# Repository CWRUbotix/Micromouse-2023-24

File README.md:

# Micromouse 2023-24 🐁

A fully autonomous maze-solving not-quite-mouse-sized robot. 

## Folders

```
.
├── LICENSE	     # License (woohoo)
├── README.md    # This file
├── cad          # 3D-models and designs
├── pcb          # Hardware-related designs and component docs
└── software     # Soft/firmware for the robot
```

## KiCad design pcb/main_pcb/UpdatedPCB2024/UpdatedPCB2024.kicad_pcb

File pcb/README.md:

# Hardware Docs & Meeting Notes

The PCB for this year's Micromouse robot makes use of several pre-built modules to simplify the pCB design. The motor drivers, accel/gyro, and Teensy 4.1 are "socketed" using headers while a custom buck/boost converter is used to generate the 5V and 3V3 rails needed by everything.

## 10/9

### TODO

* find gyro - probably i squared c 
* create Teensy on kicad
* find / reverse engineering motor controllers (DRV8871) schematics

### Parts :

* Should have
  - 6 sensors with 2 pins for i squared c and ground (software placement)
  - A voltage regulator 
  - i squared c "I2C" - protocol that is bi directional 
  - JST connectors
  - Teensy 4.1 : powerful microcontroller 
  - motor controllers : h bridge clip with capacitors 
    + can integrate into the board or kept it separate and connect manually
    + jst connectors
  - power switch
  - reset switch
  - gyro : type of sensor 
* Nice to have
  - battery protection : not required but nice to have
  - dip switches to go into debugging mode (nice to have)
  - leds for general debugging (nice to have)
  - whiteboard for labeling (nice to have)

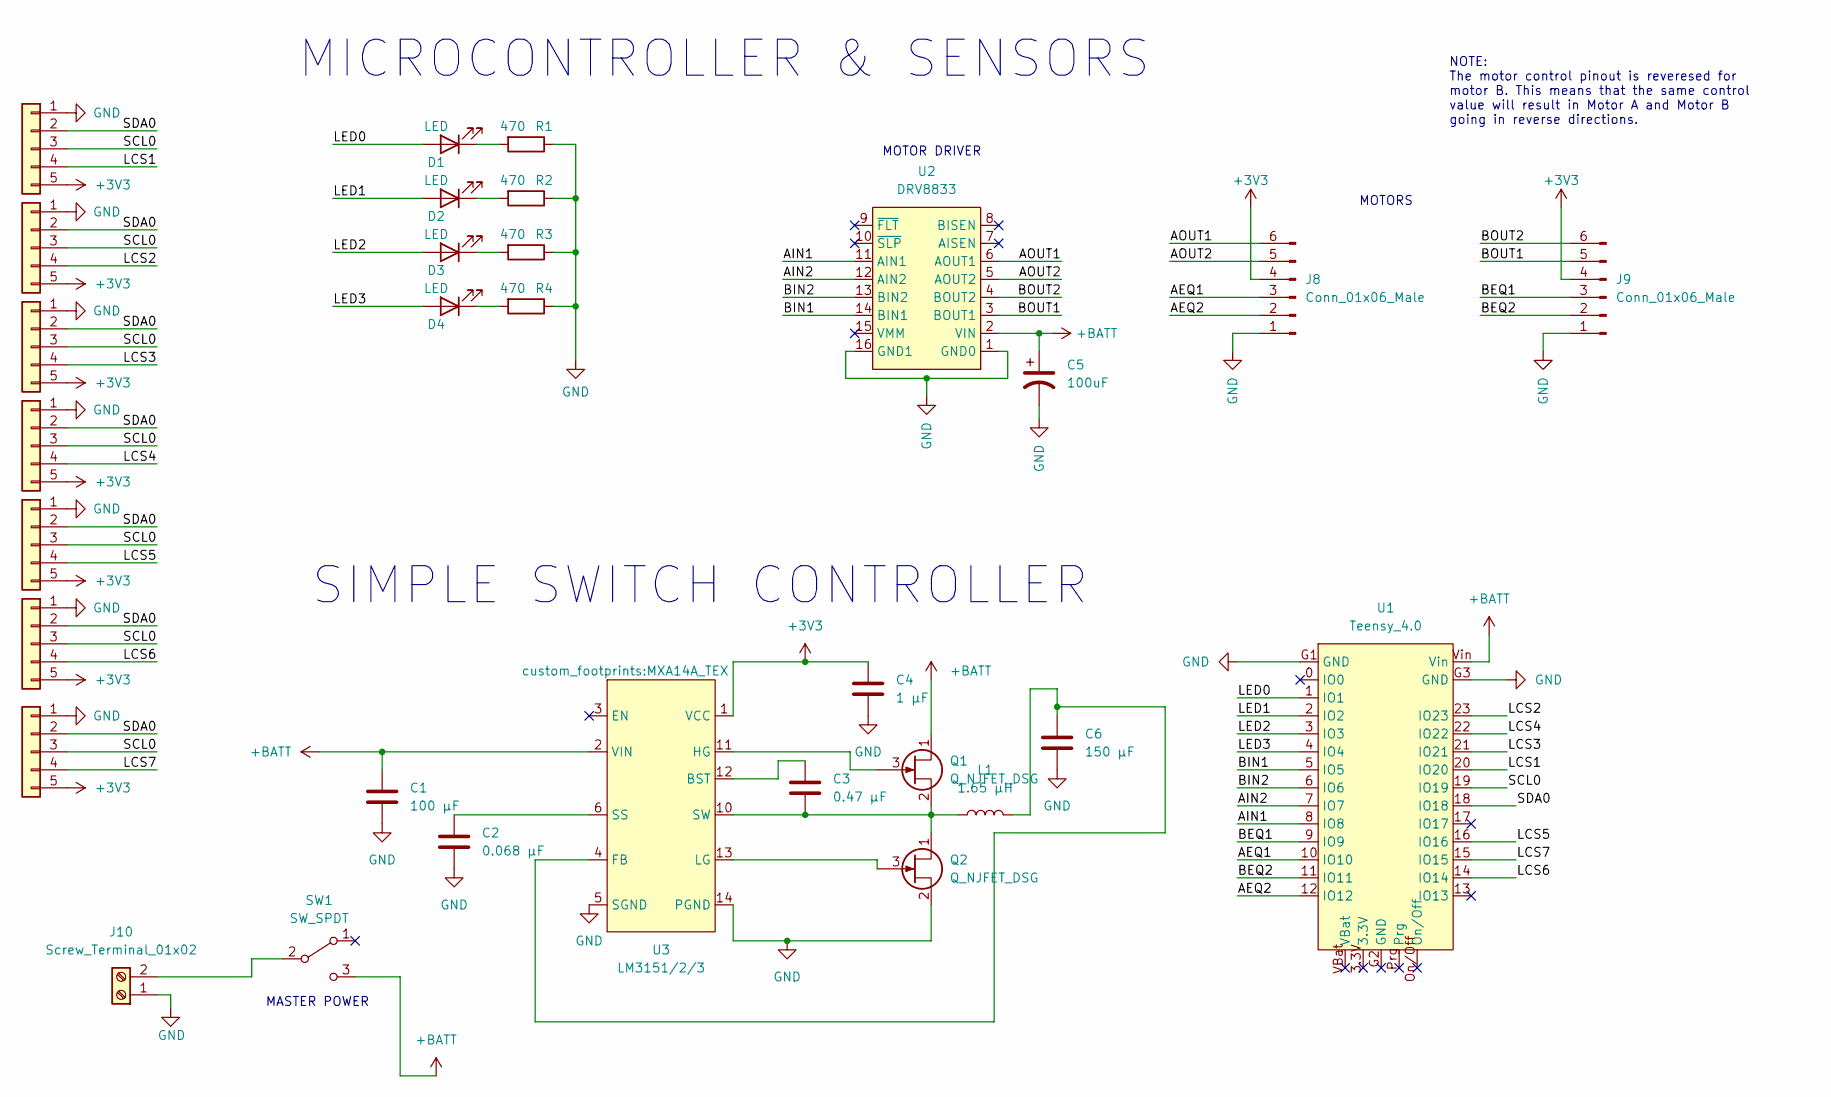
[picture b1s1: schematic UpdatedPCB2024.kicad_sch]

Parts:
C1: 100 µF; CHEMI-JA0
C2: 0.068 µF; 0603_AVX
C3: 0.47 µF; CAP_2012_TDK
C4: 1 µF; CAPC220145_100N_KEM
C5: 100uF; CP_Elec_8x10.5
C6: 150 µF; PCAP_EEF_SX_PAN
D1, D2, D3, D4: LED; LED_D5.0mm
J1, J2, J3, J4, J5, J6, J7: Conn_01x05; JST_XH_B5B-XH-A_1x05_P2.50mm_Vertical
J8, J9: Conn_01x06_Male; JST_XH_B6B-XH-A_1x06_P2.50mm_Vertical
J10: Screw_Terminal_01x02; TerminalBlock_bornier-2_P5.08mm
L1: 1.65 µH; HA3778-AL
Q1, Q2: Q_NJFET_DSG; TRANS_RTR020N_ROM
R1, R2, R3, R4: 470; R_0603_1608Metric_Pad0.98x0.95mm_HandSolder
SW1: SW_SPDT; SW_SPDT_NKK_MS12AANW03
U1: Teensy_4.0; Teensy40
U2: DRV8833; DRV_DRV8833_Pololu_2130
U3: LM3151/2/3; MXA14A_TEX

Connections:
+3V3: C4.1, J1.5, J2.5, J3.5, J4.5, J5.5, J6.5, J7.5, J8.4, J9.4, U3.1 (VCC)
+BATT: C1.1, C5.1, Q1.1 (D), SW1.3 (C), U1.Vin, U2.2 (VIN), U3.2 (VIN)
/AEQ1: J8.3, U1.10 (IO10)
/AEQ2: J8.2, U1.12 (IO12)
/AIN1: U1.8 (IO8), U2.11 (AIN1)
/AIN2: U1.7 (IO7), U2.12 (AIN2)
/AOUT1: J8.6, U2.6 (AOUT1)
/AOUT2: J8.5, U2.5 (AOUT2)
/BEQ1: J9.3, U1.9 (IO9)
/BEQ2: J9.2, U1.11 (IO11)
/BIN1: U1.5 (IO5), U2.14 (BIN1)
/BIN2: U1.6 (IO6), U2.13 (BIN2)
/BOUT1: J9.5, U2.3 (BOUT1)
/BOUT2: J9.6, U2.4 (BOUT2)
/LCS1: J1.4, U1.20 (IO20)
/LCS2: J2.4, U1.23 (IO23)
/LCS3: J3.4, U1.21 (IO21)
/LCS4: J4.4, U1.22 (IO22)
/LCS5: J5.4, U1.16 (IO16)
/LCS6: J6.4, U1.14 (IO14)
/LCS7: J7.4, U1.15 (IO15)
/LED0: D1.2 (A), U1.1 (IO1)
/LED1: D2.2 (A), U1.2 (IO2)
/LED2: D3.2 (A), U1.3 (IO3)
/LED3: D4.2 (A), U1.4 (IO4)
/SCL0: J1.3, J2.3, J3.3, J4.3, J5.3, J6.3, J7.3, U1.19 (IO19)
/SDA0: J1.2, J2.2, J3.2, J4.2, J5.2, J6.2, J7.2, U1.18 (IO18)
GND: C1.2, C2.2, C4.2, C5.2, C6.2, J1.1, J2.1, J3.1, J4.1, J5.1, J6.1, J7.1, J8.1, J9.1, J10.1, Q2.2 (S), R1.1, R2.1, R3.1, R4.1, U1.G1 (GND), U1.G3 (GND), U2.1 (GND0), U2.16 (GND1), U3.5 (SGND), U3.14 (PGND)
unnamed: D1.1 (K), R1.2
unnamed: D2.1 (K), R2.2
unnamed: D3.1 (K), R3.2
unnamed: D4.1 (K), R4.2
unnamed: J10.2, SW1.2 (B)
unnamed: Q1.3 (G), U3.11 (HG)
unnamed: C3.2, L1.2, Q1.2 (S), Q2.1 (D), U3.10 (SW)
unnamed: Q2.3 (G), U3.13 (LG)
unnamed: C3.1, U3.12 (BST)
unnamed: C6.1, L1.1, U3.4 (FB)
unnamed: C2.1, U3.6 (SS)

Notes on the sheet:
MOTORS
MOTOR DRIVER
MICROCONTROLLER & SENSORS
SIMPLE SWITCH CONTROLLER
NOTE: The motor control pinout is reveresed for motor B. This means that the same control value will result in Motor A and Motor B going in reverse directions.
MASTER POWER

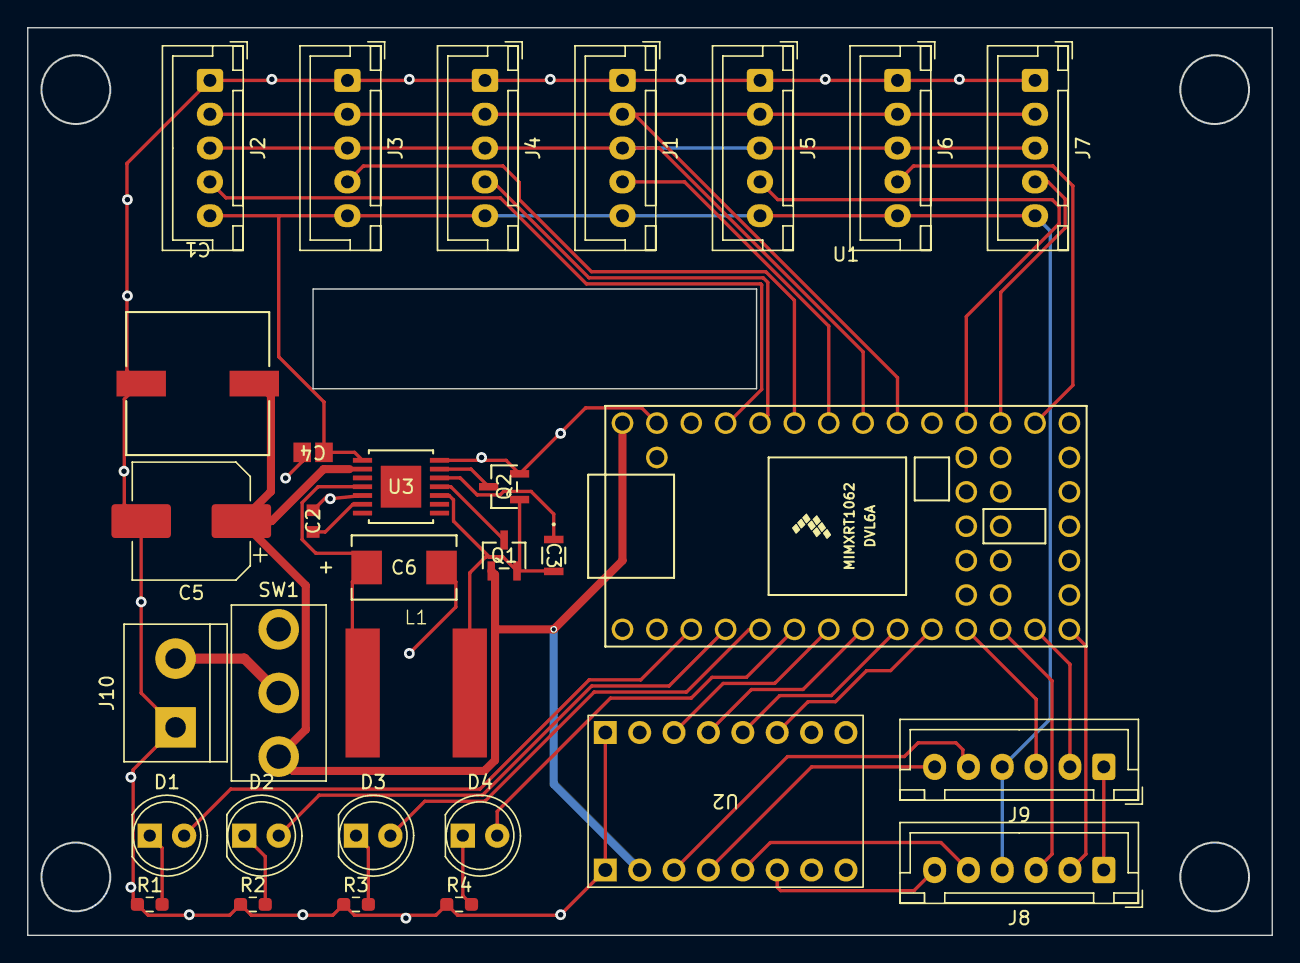
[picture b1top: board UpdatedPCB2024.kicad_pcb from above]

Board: 2 copper layers, 91.9 x 67.1 mm, 31 parts (0 on the bottom side), 39 nets.

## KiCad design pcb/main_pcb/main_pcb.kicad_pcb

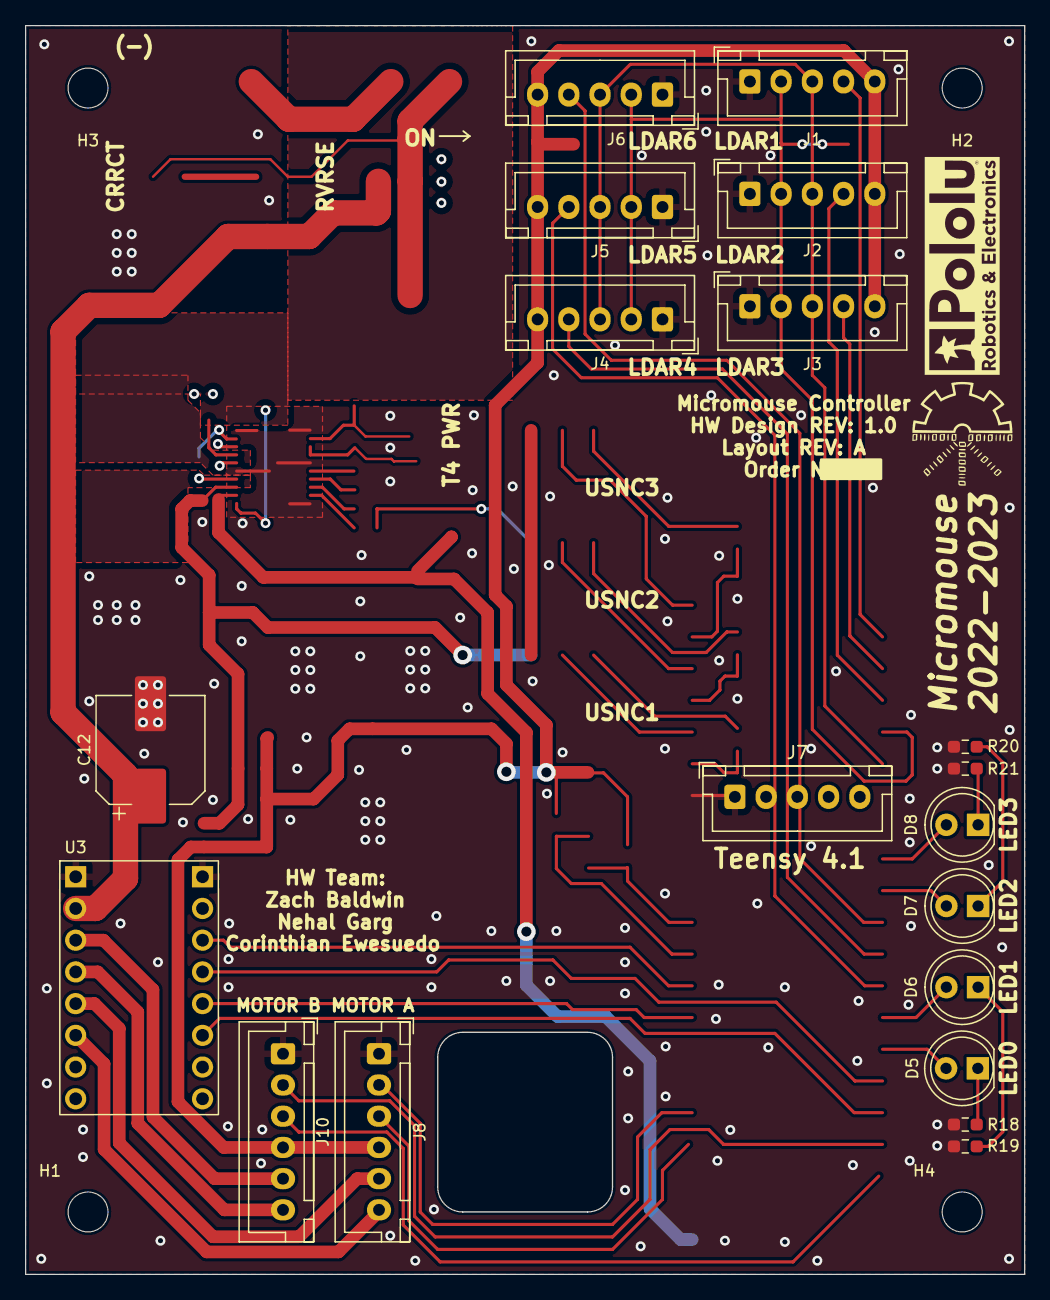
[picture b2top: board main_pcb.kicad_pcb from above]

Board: 2 copper layers, 80.0 x 100.0 mm, 23 parts (0 on the bottom side), 13 nets.

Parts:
C12: 100uF; CP_Elec_8x10.5
D5, D6, D7, D8: LED; LED_D5.0mm
H1, H2, H3, H4: MountingHole; MountingHole_3.2mm_M3
J1, J2, J3, J4, J5, J6, J7: Conn_01x05; JST_XH_B5B-XH-A_1x05_P2.50mm_Vertical
J8, J10: Conn_01x06_Male; JST_XH_B6B-XH-A_1x06_P2.50mm_Vertical
R18, R19, R20, R21: 470; R_0603_1608Metric_Pad0.98x0.95mm_HandSolder
U3: DRV8833; DRV_DRV8833_Pololu_2130

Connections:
+3V3: J1.5, J2.5, J3.5, J4.5, J5.5, J6.5, J7.5, J8.4, J10.4
+BATT: C12.1, U3.2 (VIN)
/microcontroller/AOUT1: J8.6, U3.6 (AOUT1)
/microcontroller/AOUT2: J8.5, U3.5 (AOUT2)
/microcontroller/BOUT1: J10.5, U3.3 (BOUT1)
/microcontroller/BOUT2: J10.6, U3.4 (BOUT2)
/microcontroller/SCL2: J1.3, J2.3, J3.3, J4.3, J5.3, J6.3, J7.3
/microcontroller/SDA2: J1.2, J2.2, J3.2, J4.2, J5.2, J6.2, J7.2
GND: C12.2, J1.1, J2.1, J3.1, J4.1, J5.1, J6.1, J7.1, J8.1, J10.1, R18.1, R19.1, R20.1, R21.1, U3.1 (GND0), U3.16 (GND1)
unnamed: D5.1 (K), R18.2
unnamed: D6.1 (K), R19.2
unnamed: D7.1 (K), R20.2
unnamed: D8.1 (K), R21.2

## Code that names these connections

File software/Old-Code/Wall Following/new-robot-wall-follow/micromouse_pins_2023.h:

#ifndef MICROMOUSE_PINS_2023_H
#define MICROMOUSE_PINS_2023_H

// LEDS
#define LED0 5
#define LED1 6
#define LED2 10
#define LED3 11

#ifndef _LED_ARR
#define _LED_ARR
const int LEDS[] = {LED0, LED1, LED2, LED3};
#endif

// I2C BUSES
#define I2C_LIDAR Wire2
#define I2C_GYRO Wire1

// LIDAR /CS PINS
#define LIDAR_CS1 28
#define LIDAR_CS2 26
#define LIDAR_CS3 27
#define LIDAR_CS4 8
#define LIDAR_CS5 7
#define LIDAR_CS6 9

#define SONIC_TRIG1 40
#define SONIC_TRIG2 38
#define SONIC_TRIG3 36
#define SONIC_ECHO1 41 
#define SONIC_ECHO2 39
#define SONIC_ECHO3 37

#define ENCODER_LEFT_1 22
#define ENCODER_LEFT_2 23
#define ENCODER_RIGHT_1 1
#define ENCODER_RIGHT_2 2

#define MOTORLEFT_1 3
#define MOTORLEFT_2 19
#define MOTORRIGHT_1 18
#define MOTORRIGHT_2 4
#endif

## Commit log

2022-10-04 Add incomplete 2021-22 code; init folder structure
2022-10-05 Arduino IDE changed format
2022-10-05 Updated a few TODO's
2022-10-10 Create PCB project
2022-10-10 Format meeting notes to MD; add *.zip to gitignore
2022-10-10 Rename PCB project files
2022-10-16 added schematics for DRV8871
2022-10-29 Cleaned up code a little
2022-11-04 Create teensy 4.1 and DRV8838 symbols
2022-11-04 Add Arduino-dev directory
2022-11-05 Create vl6180x example code.ino
    added lidar code
2022-11-05 Add Teensy and motor controller to sch
2022-11-11 Demonstrate Labels
2022-11-19 Add gyro symbol
2022-11-19 pcb board
2022-12-03 Checked pin-outs and added encoders to motor headers.
2022-12-16 Add Ultrasonic Sensor Testing Code
2022-12-16 Updated ultrasonic sensor test to use boolean instead of timeout
2022-12-16 Create LiDAR.ino
    Add lidar code. Not finished.
2022-12-17 Update main_pcb.kicad_sch
    add ultrasonic headers
2022-12-31 Add power regulators to schematic
2022-12-31 Annotate & begin footprint assignment
2023-01-01 Create footprints for carriers; complete footprint assignment
2023-01-03 Complete initial component placement
2023-01-03 Reorganize Teensy connections for optimized routing
2023-01-03 Set up design rules
2023-01-03 Complete digital routing
2023-01-03 More routing
2023-01-03 Complete initial routing
2023-01-03 Remote DS_Store
2023-01-03 Complete routing and Silkscreen
2023-01-05 Fix many DRC errors; correct motor B sig names
2023-01-05 Change 3V3 reg reverse diode footprint
2023-01-06 Generate gerbers
2023-01-20 Create sketch_jan20a.ino
    Testing motors
2023-01-20 Add PCB dimensions for mechanical
2023-01-20 Update sketch_jan20a.ino
    Edit to testing motors
2023-01-27 Add PCB render
2023-01-27 Code for angle/position calculation
    Calculates the angle of the robot from the "center line" of the maze path (as well as the horizontal displacement from this line) using side lidar sensors
2023-01-28 Old Robot Testing File
2023-01-28 Fixed File Upload
2023-01-31 Old Robot Config Update
2023-02-01 Delete software/Arduino-dev/Old Robot Testing directory
    Fixed Folder name change
2023-02-03 Create 90-degree turn function
2023-02-03 Updated turn function (WIP)
2023-02-06 Add initial wall following scaffold
2023-02-08 Move wall-follow.c to .ino
2023-02-09 Fix compile errors
2023-02-11 Update motor pins and test stuff
2023-02-11 Fix bug with setMotor, allow us to go backwards
2023-02-11 Start getting PID working
    * Increases motor dead zone size
    * Fixes several bugs with the PID (things not being defined, int division instead of float, etc)
    * PIDs still need tuning
2023-02-19 Update Arduino Turn Function.ino
    Added generic turn function that takes an angle input, determines direction from sign, and adjusts to accommodate for error after the turn.
2023-02-26 Update Arduino Turn Function.ino
    Fixed errors with existing code, wrote untested method to turn using a PID loop, and added Zach's lidar initialization code
2023-02-27 Add LiDAR test for new robot
2023-03-05 Add history to wall following; create new robot wall follow
2023-03-05 Create Pin Header File
    Created the pin header file with all of the pin numbers for the new robot
2023-03-05 Changed the header file to .h
    Pin header file is now a .h instead of .ino
2023-03-05 Tweaks for new robot (doesn't work right now)
2023-03-21 Add basic motor power control function
2023-03-21 Update new robot encoder right pins; fix distance tracking
2023-03-21 Clean up setMotor()
2023-03-21 Remove backup and exported STEP PCB files
2023-03-21 Renamed turning file and tested PID
2023-03-24 Update lidar for new robots
2023-03-24 Fix motors for new robot
2023-03-24 Added second lidar calculation
2023-03-24 Fix types and get angle PID kind of working!
2023-03-26 Added documentation to turning functions
2023-03-26 IT KIND OF WORKS!
2023-03-28 Go 3 instead of 1 square
2023-03-28 Elegantly stop using sensors that have read errors & remove LPF
2023-03-28 Add ASCII art diagraming centering math
2023-03-28 Center the robot in the hallway
2023-03-28 Move ASCII art into code
2023-03-28 Add missing else!
2023-03-29 Add missing break
2023-04-01 Integrate movement into Micromouse.ino
    This commit is completely untested.
2023-04-02 Read sensor data to update maze information
2023-04-02 Mostly solve maze!
2023-04-04 Add print statements for debugging A*
2023-04-04 Fix major bug with backPath creation
2023-04-04 Add code to get forward distance from ultrasonic
2023-04-04 Use LEDs, go to center of 4x4
2023-04-04 Turn off LED
2023-04-07 Added TurnDirection method
    Temp. Just trying to condense code
2023-04-07 Use ultrasonic to update maze
2023-04-07 Updated turn method
2023-04-07 Removed unneeded methods
2023-04-09 Scale motor power by 0.7
    The motors are 6V motors but we're running that at a max of 9V. This isn't a problem from a hardware perspective, we just don't want to go too fast.
2023-04-09 Created getAngle method
2023-04-09 updated getAngle rotate
2023-04-10 Add ultrasonic check to not crash into front wall
2023-04-11 MAPPING_MODE refactor
2023-04-11 Fix 2 bugs and fix forward accumulated error
    * First bug: since the ultrasonic running average was only being updated if there was a wall in front of us, in practice, the average was often less than 60. This meant that this code would stop us w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
    * Second bug: Turing was accumulating error half the time.
    * Fix forward accumulated error (if we haven't moved as far down a long hallway as we should have) by checking the ultrasonic before we stop moving forward.
2023-04-11 Fix bug with path creation
2023-04-11 Turn with the average of both encoders
    * Tweak some delays (the faster the better)
2023-04-13 Untested Flood Fill code
2023-04-13 Fix terrible bug with FF
2023-04-14 Add long press mode switch
2023-05-08 Add custom footprints
2023-05-08 Add cwrubotix and Pololu logos
2023-11-01 Added Teensy 4.0 schematic
2023-11-01 Adding LCS branches
2023-11-01 Finishing LCS wires
2023-11-03 Added flood fill algorithm draft
2023-11-07 new changes to pcb
2023-11-08 deleted ultrasonic sensors
2023-11-08 changed ultrasonic placement on teensy 4.0
2023-11-08 deleted digital 5V power supply
2023-11-08 title change
2023-11-10 added leftwallfollow, conversion in progress for testing
2023-11-15 Got flood fill code working with MMS
    There seems to be an error in the code, particularly noticeable in the fifth preset layout, where the robot will prioritize moving to cells that are clearly not optimal based on the information avail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
2023-11-15 Deleted old 3v3 power supply
2023-11-15 simple switcher controller
2023-11-15 simple switch controller addition
2023-11-17 Split code into three respective files
2023-11-17 Added .vscode files to gitignore
2023-11-17 Added sim c code
2023-11-18 Fixed Sim - Maze is intuitive orientation
2023-11-21 adjustment to simple switch controller
2023-11-22 ADDED MOSFETS
2023-11-22 small changes
2023-12-01 Made maze size and goal soft-coded
2023-12-01 Tweaked initial maze turns
2023-12-01 Updated floodfill to support backtracking
2023-12-01 Updated Sim
2023-12-01 Updated coordinate system in previous commit
    Updated coordinates in internal logic to be consistent with coordinate system used by simulator
2023-12-01 API changed
2023-12-04 Separated algorithm and simulator interface
2023-12-11 temp
2023-12-16 changes to pcb
2024-01-01 last minute changes
2024-01-20 Organized code
2024-01-25 Path traversal and robot integration
2024-01-26 Wrote circle turning function
2024-01-26 updated turning function
2024-01-26 libraries
2024-01-26 Added comments and other misc. fixes
2024-01-26 Finished Integration
2024-02-01 Tweaks
2024-02-01 Updated turning code WIP
2024-02-02 Error corrections
2024-02-02 Updated for edge-to-edge square movement
2024-02-09 Combined moveForward functions
2024-02-09 Tweaks for errors
2024-02-09 Implemented new turning code
2024-02-10 Fixed turning code
2024-02-13 newfilePCB
2024-02-13 Footprint and labelling
    Added the Teensy40 footprint into the custom-footprints.pretty folder, which will allow us to link the teensy40 footprint to the schematic we have. will still need to be readdressed.
    Changed the raw text on the schematic to labels so that they will be recognized as connections rather than just text.
2024-02-13 Symbol footprint linking for teensy4
    Changed some numbers and names around so that the footprint properly linked to the symbol for the Teensy4.0
    We still need to assign footprints to the other circuit components that are not yet assigned, as well as update symbols as necessary.
2024-02-14 Fixed multiple user issue
    Previously, when pulled the custom footprints library in the update 2024 pcb section was set to be my specific library path. I changed it to be more general so it should work out of the gate for ever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
2024-02-16 Fixed moving/turning
2024-02-16 Including footprints for most pcb parts
2024-02-16 adding footprints continued
2024-02-16 Finished updating algorithm movement changes
2024-02-16 API additions
2024-02-16 Fixed some variable types in Mouse.ino
2024-02-16 Standardized simulator/robot interface somewhat
2024-02-20 Created L1 footprint
    Created L1 footprint from product datasheet's recommended footprint.
2024-02-20 fixing errors on PCB as well as readjustments to outline of PCB
2024-02-23 Simple switch controller layout
    Did the layout for the simple switch controller such that the pathing is easy.
2024-02-23 Adjusted constants in turning code
2024-02-24 Updated a large portion of the code to adjust for using the LIDARs instead of Ultrasonic sensors
2024-02-29 Edited schematic + layout
    Changed some pin configurations (made sure SDA and SCL are configured properly, as well as all PWM necessary pins) and began routing. Layout at this point is finalized, needs to be reviewed and appro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
2024-03-01 API addition/Switched int to double in moveForward
2024-03-02 Completed updating code for the new robot
2024-03-05 Routing done, DRC pass
    Finsihed layout and routing, filled ground plane, and added vias to tie off ground plane.
2024-03-06 Generated Gerber file and finished board
    Its done! yippeeee!
    Added some holes, made some routes thicker, reran the filling functions etc. etc.
2024-03-22 Fixed wall detection
2024-03-22 Removed moveForwardHalf
2024-03-22 Fixed direction - added constants
2024-03-23 Changed gearRatio to 150
2024-03-29 Fixed moving forward
2024-03-29 Fixed moving turn
2024-03-29 Fixed moving forward by eliminating the multiplying by values of the P controller (#8)
    * Fixed moving forward
    * Fixed moving turn
2024-03-30 Reverted to old movement for Algo
2024-03-30 Changed param back to int in moveForward
2024-04-05 Updated the encoderTicks through wheelRadius to be the dimensions for the new robot
2024-04-05 updated lidar_front_offset
2024-04-06 fixed a typo
2024-04-06 Updated pins
2024-04-06 Added debug msgs
2024-04-07 Finished the pins and mapping in the pins file
2024-04-07 Changed Lidar pins array to new system to make it easier to understand
2024-04-13 Updated all constants to be in terms of mm
2024-04-13 Slowed down moveForward
2024-04-14 Made angle Tolerance -30;Now subtract angles in turnLeft
2024-04-19 Enumerated speeds, different ultrasonic wall bound, explicit wall checking (Competition commit
2024-09-13 Added Software Setup README
2024-09-21 Adjusted input mode as per Max's instructions
2024-09-28 Adjusted constant values for new robot
2024-10-05 Revert "Changed param back to int in moveForward"
    This reverts commit ce270a8f43eaf3963b7952ab9bd809c3083c76e3.
2024-10-05 Revert "Fixed moving forward by eliminating the multiplying by values of the P controller (#8)"
    This reverts commit df265add56fc8e140ef522fb9257ae3f8838fe75.
2024-10-05 Refactored software directory
2024-10-12 Uncommented DEBUG_LED pin
2024-10-12 cleaning
    - cleaned wall detection
    - cleaned sensor ouputs
2024-11-09 11/9 Package Initialization
    This push is meant to add all of the dependencies for Arduino and LIDARs to the branch.
